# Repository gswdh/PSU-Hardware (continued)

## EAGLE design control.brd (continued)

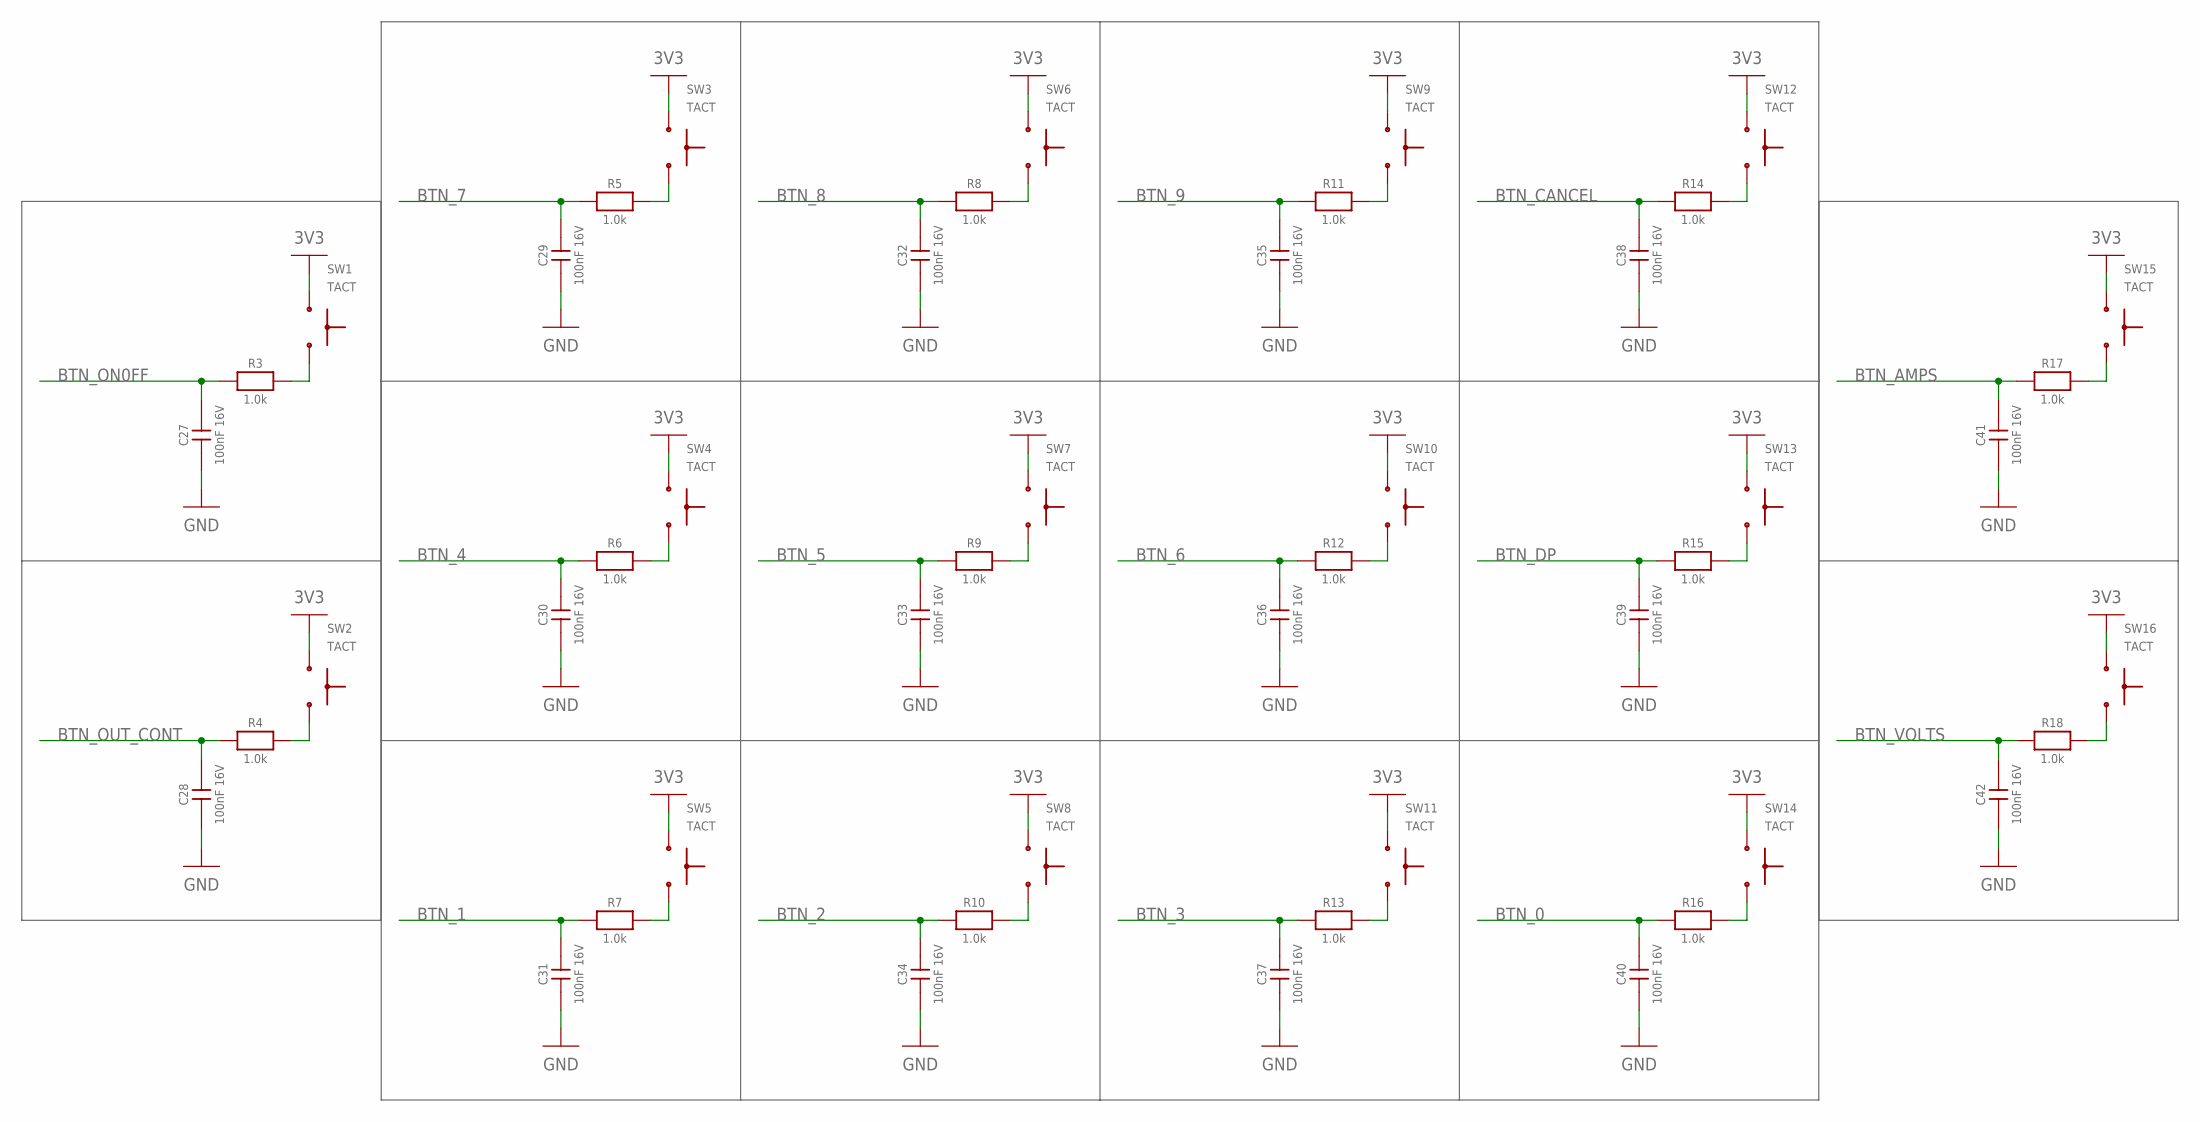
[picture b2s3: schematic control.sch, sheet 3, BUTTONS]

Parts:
C27, C28, C29, C30, C31, C32, C33, C34, C35, C36, C37, C38, C39, C40, C41, C42: 100nF 16V; 0603
R3, R4, R5, R6, R7, R8, R9, R10, R11, R12, R13, R14, R15, R16, R17, R18: 1.0k; 0603
SW1, SW2, SW3, SW4, SW5, SW6, SW7, SW8, SW9, SW10, SW11, SW12, SW13, SW14, SW15, SW16: TACT; TL1100DF160Q

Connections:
3V3: SW1.1, SW1.3 (1), SW2.1, SW2.3 (1), SW3.1, SW3.3 (1), SW4.1, SW4.3 (1), SW5.1, SW5.3 (1), SW6.1, SW6.3 (1), SW7.1, SW7.3 (1), SW8.1, SW8.3 (1), SW9.1, SW9.3 (1), SW10.1, SW10.3 (1), SW11.1, SW11.3 (1), SW12.1, SW12.3 (1), SW13.1, SW13.3 (1), SW14.1, SW14.3 (1), SW15.1, SW15.3 (1), SW16.1, SW16.3 (1); also elsewhere on the board
BTN_0: C40.2, R16.1; also elsewhere on the board
BTN_1: C31.2, R7.1; also elsewhere on the board
BTN_2: C34.2, R10.1; also elsewhere on the board
BTN_3: C37.2, R13.1; also elsewhere on the board
BTN_4: C30.2, R6.1; also elsewhere on the board
BTN_5: C33.2, R9.1; also elsewhere on the board
BTN_6: C36.2, R12.1; also elsewhere on the board
BTN_7: C29.2, R5.1; also elsewhere on the board
BTN_8: C32.2, R8.1; also elsewhere on the board
BTN_9: C35.2, R11.1; also elsewhere on the board
BTN_AMPS: C41.2, R17.1; also elsewhere on the board
BTN_CANCEL: C38.2, R14.1; also elsewhere on the board
BTN_DP: C39.2, R15.1; also elsewhere on the board
BTN_ON0FF: C27.2, R3.1; also elsewhere on the board
BTN_OUT_CONT: C28.2, R4.1; also elsewhere on the board
BTN_VOLTS: C42.2, R18.1; also elsewhere on the board
GND: C27.1, C28.1, C29.1, C30.1, C31.1, C32.1, C33.1, C34.1, C35.1, C36.1, C37.1, C38.1, C39.1, C40.1, C41.1, C42.1; also elsewhere on the board
unnamed: R3.2, SW1.2, SW1.4 (2)
unnamed: R4.2, SW2.2, SW2.4 (2)
unnamed: R5.2, SW3.2, SW3.4 (2)
unnamed: R6.2, SW4.2, SW4.4 (2)
unnamed: R7.2, SW5.2, SW5.4 (2)
unnamed: R8.2, SW6.2, SW6.4 (2)
unnamed: R9.2, SW7.2, SW7.4 (2)
unnamed: R10.2, SW8.2, SW8.4 (2)
unnamed: R11.2, SW9.2, SW9.4 (2)
unnamed: R12.2, SW10.2, SW10.4 (2)
unnamed: R13.2, SW11.2, SW11.4 (2)
unnamed: R14.2, SW12.2, SW12.4 (2)
unnamed: R15.2, SW13.2, SW13.4 (2)
unnamed: R16.2, SW14.2, SW14.4 (2)
unnamed: R17.2, SW15.2, SW15.4 (2)
unnamed: R18.2, SW16.2, SW16.4 (2)

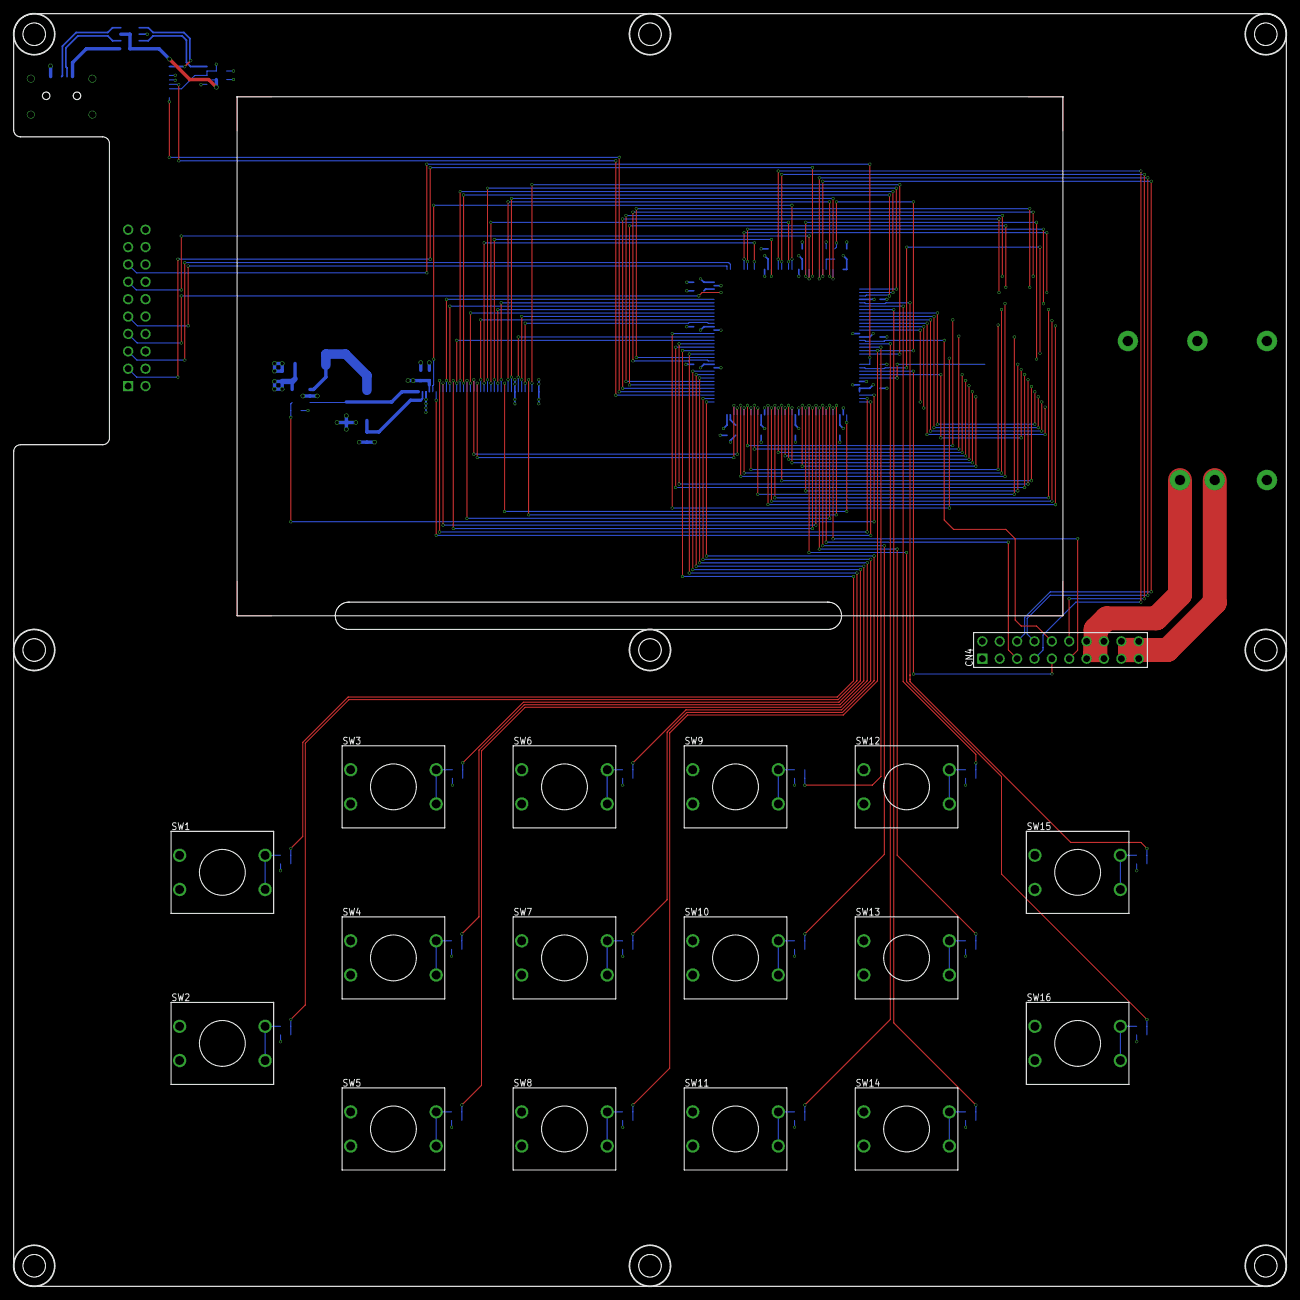
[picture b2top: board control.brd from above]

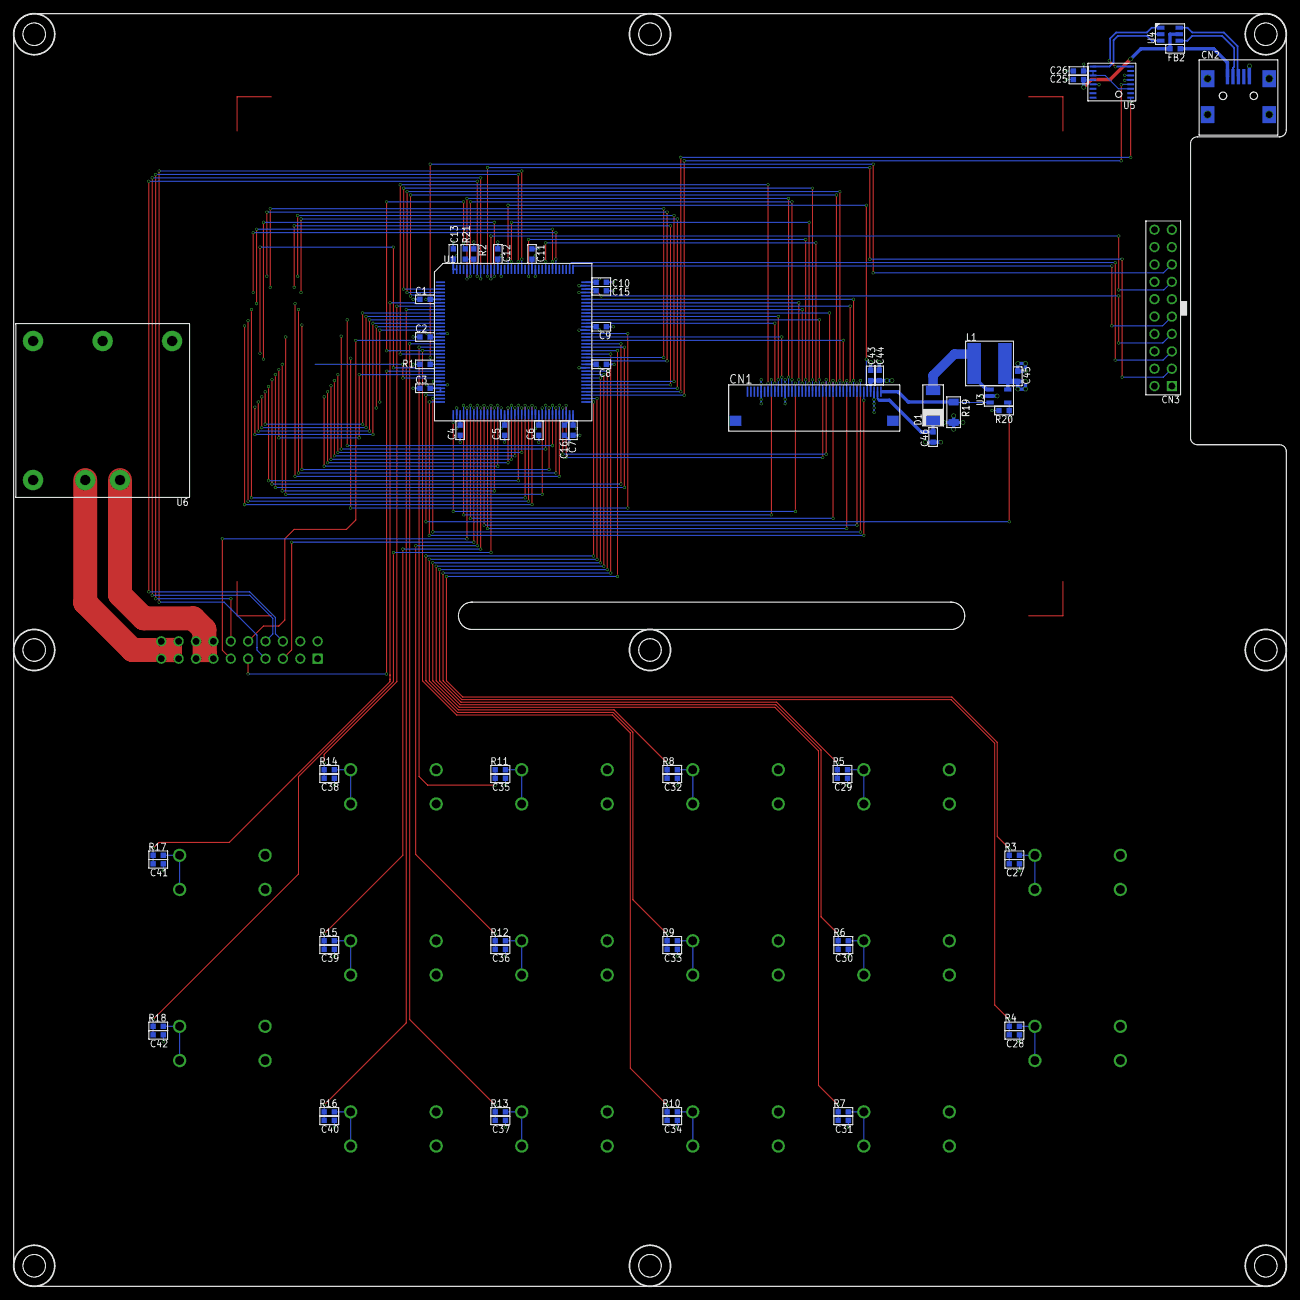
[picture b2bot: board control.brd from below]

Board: 4 copper layers, 186.0 x 186.0 mm, 95 parts (69 on the bottom side), 95 nets.

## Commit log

2020-09-30 The start
2020-09-30 Simulation added
2020-09-30 Work on the control
2020-10-03 Progress on PCBs
2020-10-06 Progress
2020-10-08 Control nearly done
2020-10-08 Stencil for button added
2020-10-08 Female header added to the power PCB
2020-10-08 DRC passes on both PCBs, pushed to Fusion
2020-10-08 Bridge connector fixed
2020-10-08 Checked against Cube
2020-10-09 Updated libs with digikey numbers
2020-10-09 BoM sorted for the power PCB
2020-10-09 Added control for the output relay
2020-10-11 Corrected JTAG pinout
2020-10-11 Button screens screated
2020-10-11 Latest in Fusion and GERBERs generated
2020-10-26 GUI designed in Eagle
2020-10-30 Fixes for stability
2020-11-01 Removed media objects
